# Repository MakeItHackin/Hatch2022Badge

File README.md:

# Hatch2022Badge

Thank you for being interested in this year's Hudson Alpha Tech Challenge Badge!!!  

View my YouTube video for a quick demo and overview:  
https://www.youtube.com/watch?v=n5ird6Otu6U

The badges were designed by @MakeItHackin and sponsored by Hudson Alpha.  

The badge is in the shape of the Hudson Alpha logo.  It features a fully functioning circuit if you would like to solder components onto the top surface.  Using a 555 timer and a 4017 Decade Counter, the 10 LEDs will flash one by one.  Using the "speed" switch, the user can either pick a slow or fast blinking mode for the LEDs.  

If you have any questions or comments, please initiate an 'Issue' on github and I will answer as soon as I can.

Below are the components that can be soldered onto the badge for functionality:
CR2032 Battery and Holder
555 Timer
4017 Decade Counter
100 ohm 0805 resistors 
0805 LEDs
Two switches
Two capacitors (4.7uF and 22uF for changing speed)
Two 22kohm resistors for 555 timer

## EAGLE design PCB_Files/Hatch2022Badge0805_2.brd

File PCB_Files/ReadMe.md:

There are two files.  Created using Autodesk Eagle  
SCH file is the Electrical Schematic  
BRD file is the Board Diagram

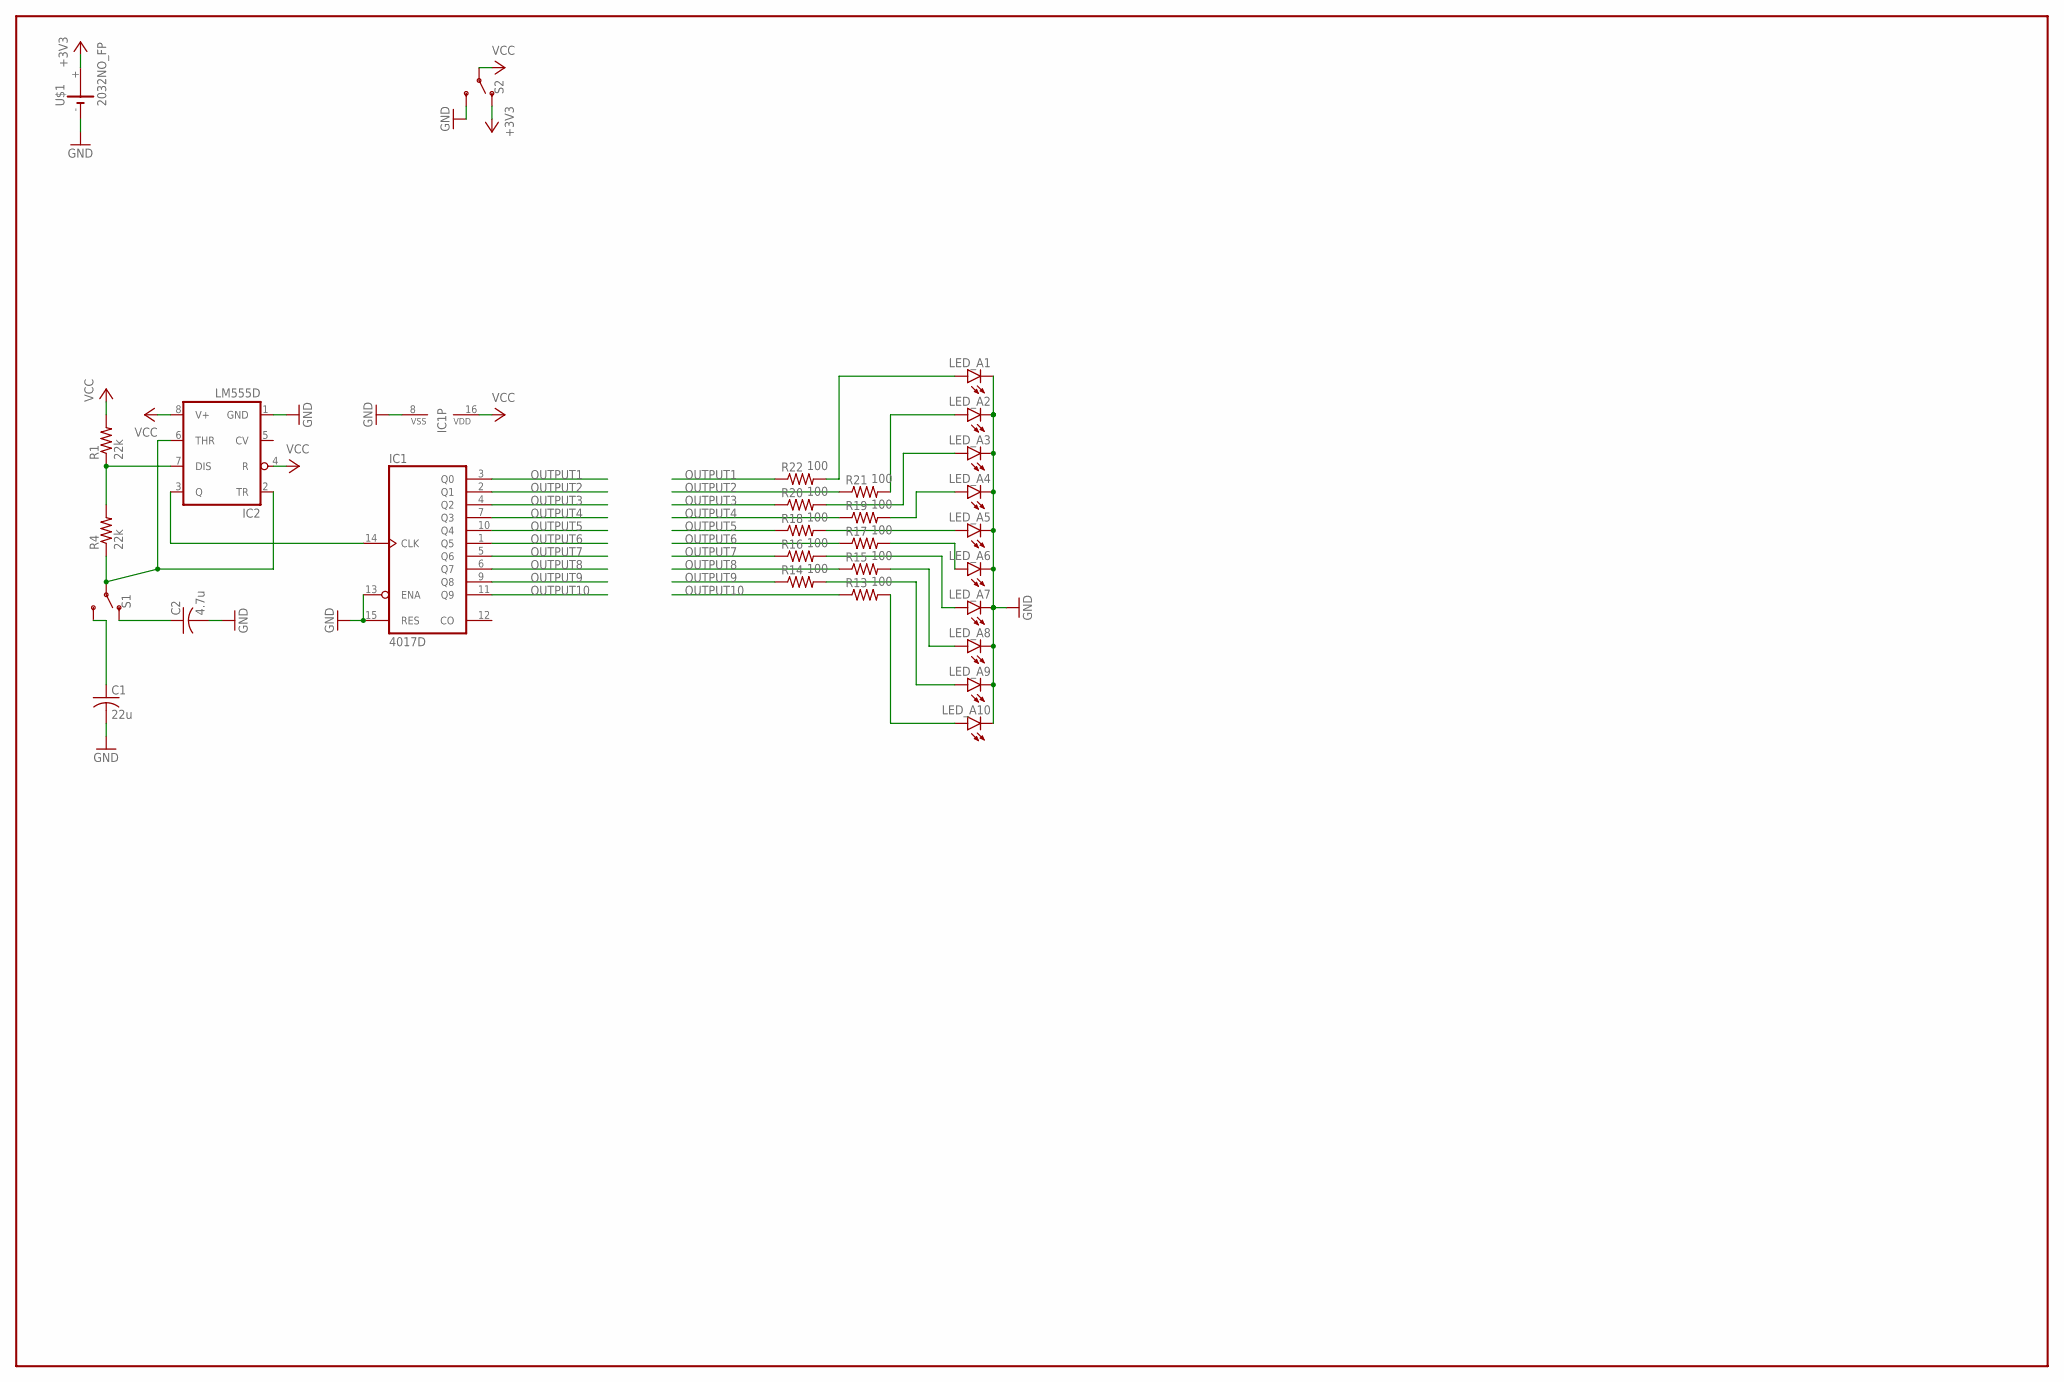
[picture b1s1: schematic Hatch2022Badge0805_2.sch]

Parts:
C1: 22u; C0805
C2: 4.7u; C0805
IC1: 4017D; SO16
IC2: LM555D; SO08
LED_A1, LED_A2, LED_A3, LED_A4, LED_A5, LED_A6, LED_A7, LED_A8, LED_A9, LED_A10: LEDSML0805; SML0805
R1, R4: 22k; R0805
R13, R14, R15, R16, R17, R18, R19, R20, R21, R22: 100; R0805
S1, S2: SWITCH-SPDT-SMD-AYZ0202; SWITCH_DPDT_SMD_AYZ0202
U$1: 2032NO_FP; 2032_NO_FP

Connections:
+3V3: S2.1 (O), U$1.+
GND: C1.2, C2.2, IC1.8 (VSS), IC1.13 (ENA), IC1.15 (RES), IC2.1 (GND), LED_A1.C, LED_A2.C, LED_A3.C, LED_A4.C, LED_A5.C, LED_A6.C, LED_A7.C, LED_A8.C, LED_A9.C, LED_A10.C, S2.3 (S), U$1.-
unnamed: IC2.7 (DIS), R1.1, R4.2
unnamed: LED_A2.A, R21.2
unnamed: LED_A3.A, R20.2
unnamed: C1.1, S1.3 (S)
unnamed: C2.1, S1.1 (O)
unnamed: LED_A1.A, R22.2
unnamed: LED_A4.A, R19.2
unnamed: LED_A5.A, R18.2
unnamed: LED_A6.A, R17.2
unnamed: LED_A7.A, R16.2
unnamed: LED_A8.A, R15.2
unnamed: LED_A9.A, R14.2
unnamed: LED_A10.A, R13.2
unnamed: IC2.2 (TR), IC2.6 (THR), R4.1, S1.2
unnamed: IC1.14 (CLK), IC2.3 (Q)
OUTPUT1: IC1.3 (Q0), R22.1
OUTPUT2: IC1.2 (Q1), R21.1
OUTPUT3: IC1.4 (Q2), R20.1
OUTPUT4: IC1.7 (Q3), R19.1
OUTPUT5: IC1.10 (Q4), R18.1
OUTPUT6: IC1.1 (Q5), R17.1
OUTPUT7: IC1.5 (Q6), R16.1
OUTPUT8: IC1.6 (Q7), R15.1
OUTPUT9: IC1.9 (Q8), R14.1
OUTPUT10: IC1.11 (Q9), R13.1
VCC: IC1.16 (VDD), IC2.4 (R), IC2.8 (V+), R1.2, S2.2

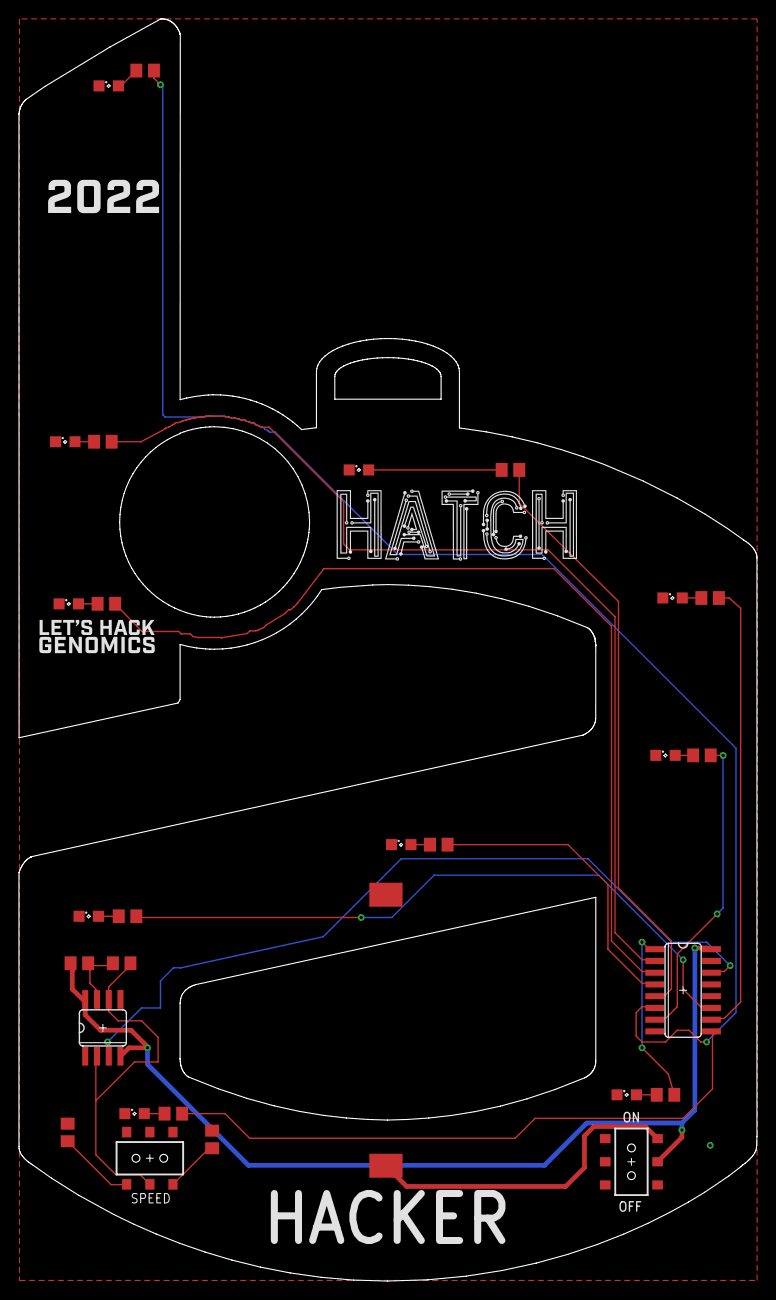
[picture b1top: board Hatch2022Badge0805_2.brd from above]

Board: 2 copper layers, 79.8 x 136.5 mm, 29 parts (0 on the bottom side), 28 nets.

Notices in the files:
parts and their libraries:
SparkFun-Switches: Licensing: Creative Commons ShareAlike 4.0 International - https://creativecommons.org/licenses/by-sa/4.0
